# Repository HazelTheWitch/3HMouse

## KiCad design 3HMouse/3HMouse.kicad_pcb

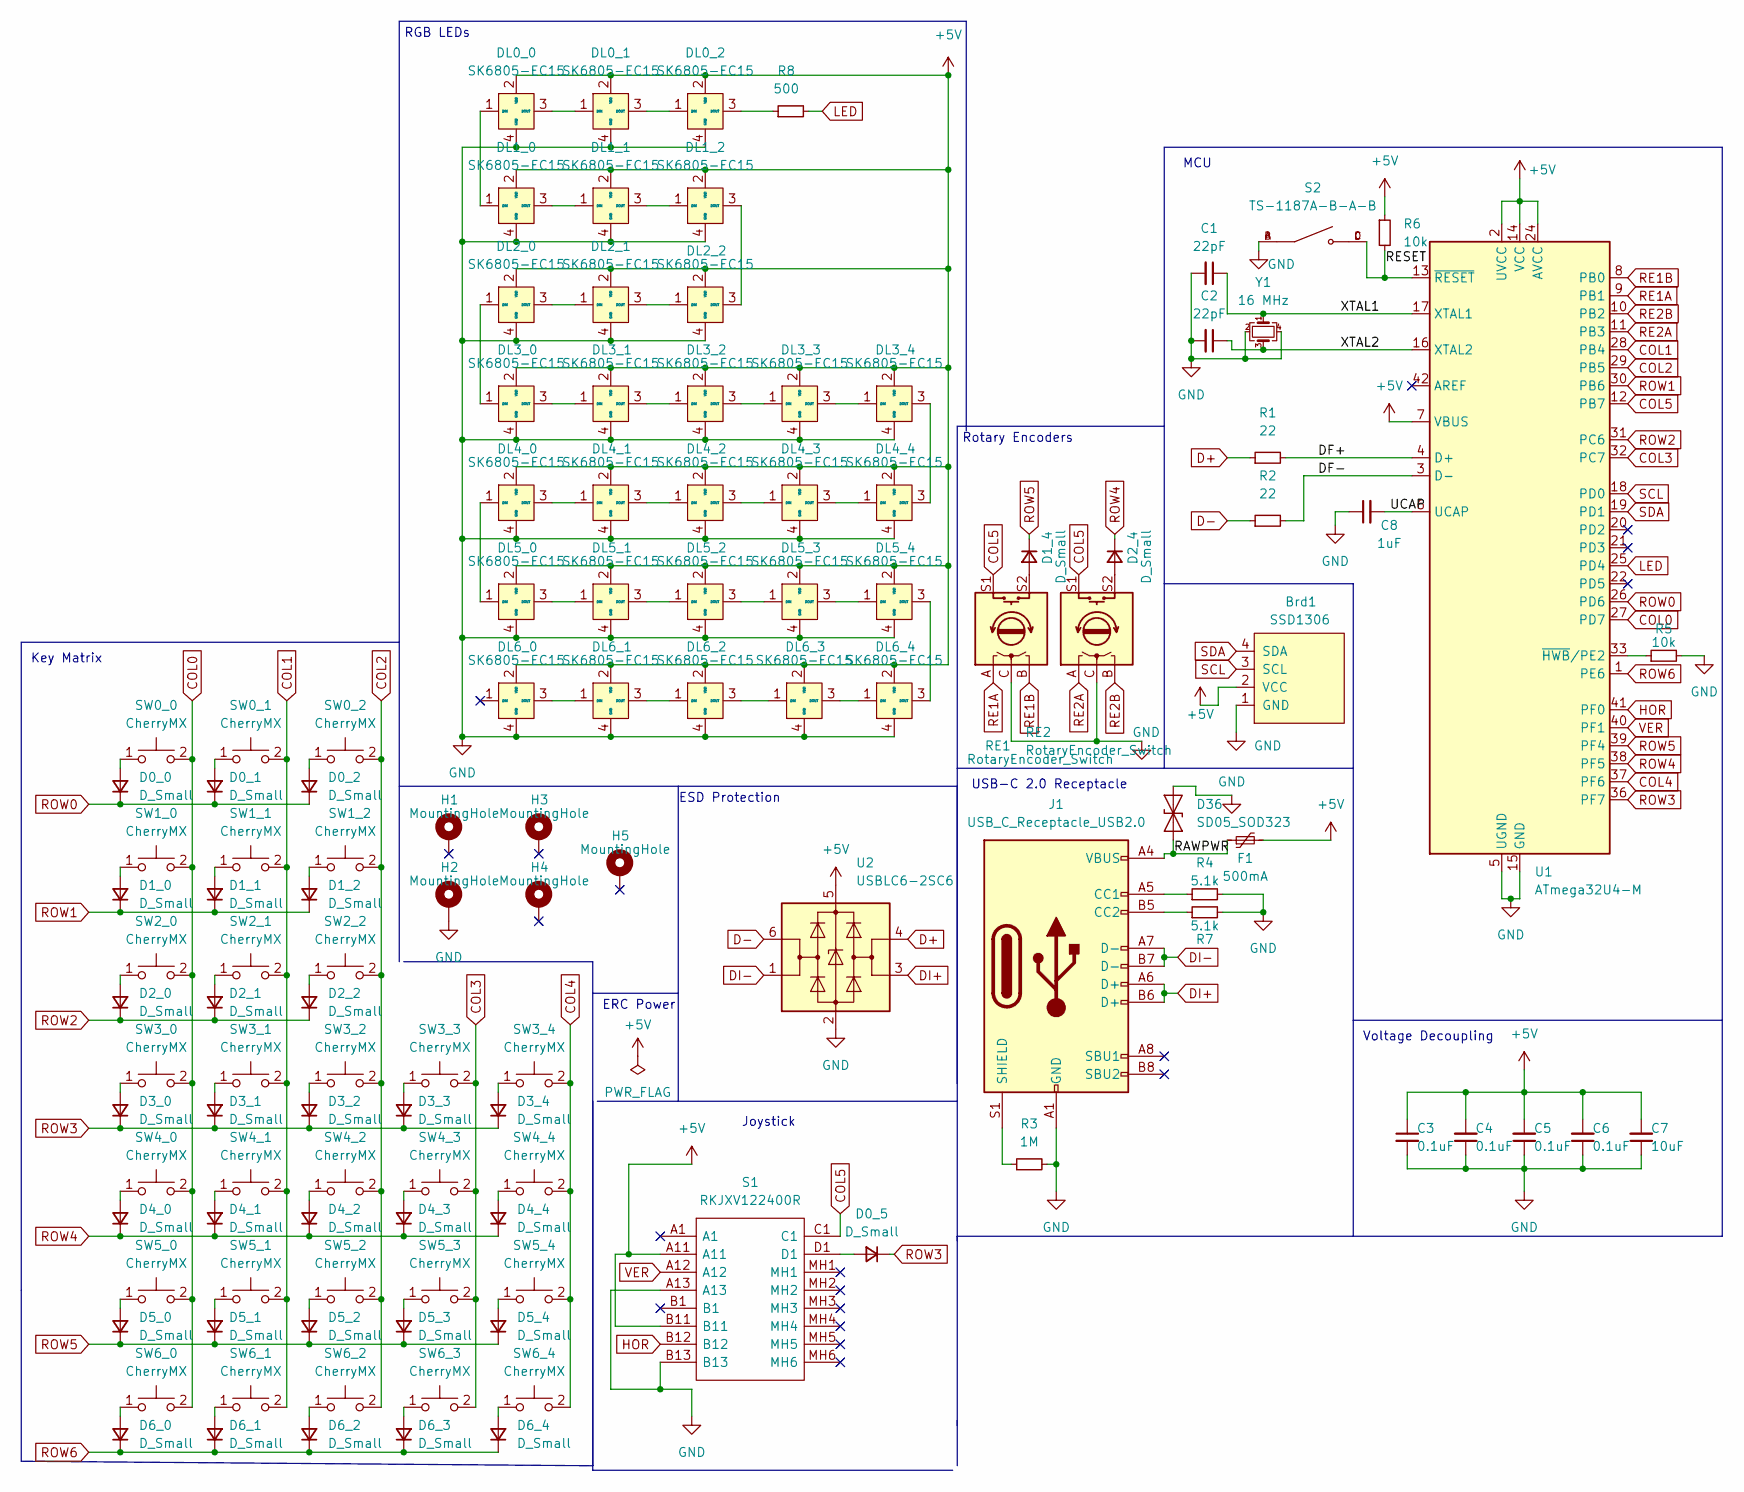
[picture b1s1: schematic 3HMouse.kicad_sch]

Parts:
Brd1: SSD1306; 128x64OLED
C1, C2: 22pF; C_0805_2012Metric
C3, C4, C5, C6: 0.1uF; C_0805_2012Metric
C7: 10uF; C_0805_2012Metric
C8: 1uF; C_0805_2012Metric
D0_0, D0_1, D0_2, D0_5, D1_0, D1_1, D1_2, D1_4, D2_0, D2_1, D2_2, D2_4, D3_0, D3_1, D3_2, D3_3, D3_4, D4_0, D4_1, D4_2, D4_3, D4_4, D5_0, D5_1, D5_2, D5_3, D5_4, D6_0, D6_1, D6_2, D6_3, D6_4: D_Small; D_SOD-123
D36: SD05_SOD323; D_SOD-323
DL0_0, DL0_1, DL0_2, DL1_0, DL1_1, DL1_2, DL2_0, DL2_1, DL2_2, DL3_0, DL3_1, DL3_2, DL3_3, DL3_4, DL4_0, DL4_1, DL4_2, DL4_3, DL4_4, DL5_0, DL5_1, DL5_2, DL5_3, DL5_4, DL6_0, DL6_1, DL6_2, DL6_3, DL6_4: SK6805-EC15
F1: 500mA; Fuse_1206_3216Metric
H1, H2, H3, H4, H5: MountingHole; MountingHole_2.2mm_M2_Pad
J1: USB_C_Receptacle_USB2.0; USB_C_Receptacle_GT-USB-7010
R1, R2: 22; R_0805_2012Metric
R3: 1M; R_0805_2012Metric
R4, R7: 5.1k; R_0805_2012Metric
R5, R6: 10k; R_0805_2012Metric
R8: 500; R_0805_2012Metric
RE1, RE2: RotaryEncoder_Switch; RotaryEncoder_Alps_EC11E-Switch_Vertical_H20mm
S1: RKJXV122400R; Mouser Part Number 688-RKJXV122400R
S2: TS-1187A-B-A-B; SW_TS-1187A-B-A-B; PARTREV A0
SW0_0, SW0_1, SW0_2, SW1_0, SW1_1, SW1_2, SW2_0, SW2_1, SW2_2, SW3_0, SW3_1, SW3_2, SW3_3, SW3_4, SW4_0, SW4_1, SW4_2, SW4_3, SW4_4, SW5_0, SW5_1, SW5_2, SW5_3, SW5_4, SW6_0, SW6_1, SW6_2, SW6_3, SW6_4: CherryMX; MXOnly-1U-Hotswap
U1: ATmega32U4-M; QFN-44-1EP_7x7mm_P0.5mm_EP5.2x5.2mm
U2: USBLC6-2SC6; SOT-23-6
Y1: 16 MHz; Crystal_SMD_3225-4Pin_3.2x2.5mm

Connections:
+5V: Brd1.2 (VCC), C3.1, C4.2, C5.2, C6.2, C7.2, DL0_0.2 (VDD), DL0_1.2 (VDD), DL0_2.2 (VDD), DL1_0.2 (VDD), DL1_1.2 (VDD), DL1_2.2 (VDD), DL2_0.2 (VDD), DL2_1.2 (VDD), DL2_2.2 (VDD), DL3_0.2 (VDD), DL3_1.2 (VDD), DL3_2.2 (VDD), DL3_3.2 (VDD), DL3_4.2 (VDD), DL4_0.2 (VDD), DL4_1.2 (VDD), DL4_2.2 (VDD), DL4_3.2 (VDD), DL4_4.2 (VDD), DL5_0.2 (VDD), DL5_1.2 (VDD), DL5_2.2 (VDD), DL5_3.2 (VDD), DL5_4.2 (VDD), DL6_0.2 (VDD), DL6_1.2 (VDD), DL6_2.2 (VDD), DL6_3.2 (VDD), DL6_4.2 (VDD), F1.2, R6.1, S1.A11, S1.B11, U1.2 (UVCC), U1.7 (VBUS), U1.14 (VCC), U1.24 (AVCC), U1.34 (VCC), U1.44 (AVCC), U2.5 (VBUS)
/DF+: R1.2, U1.4 (D+)
/DF-: R2.2, U1.3 (D-)
/RAWPWR: D36.1 (A1), F1.1, J1.A4 (VBUS), J1.A9 (VBUS), J1.B4 (VBUS), J1.B9 (VBUS)
/RESET: R6.2, S2.C, S2.D, U1.13 (~RESET)
/UCAP: C8.2, U1.6 (UCAP)
/XTAL1: C1.1, U1.17 (XTAL1), Y1.1
/XTAL2: C2.1, U1.16 (XTAL2), Y1.3
COL0: SW0_0.2, SW1_0.2, SW2_0.2, SW3_0.2, SW4_0.2, SW5_0.2, SW6_0.2, U1.27 (PD7)
COL1: SW0_1.2, SW1_1.2, SW2_1.2, SW3_1.2, SW4_1.2, SW5_1.2, SW6_1.2, U1.28 (PB4)
COL2: SW0_2.2, SW1_2.2, SW2_2.2, SW3_2.2, SW4_2.2, SW5_2.2, SW6_2.2, U1.29 (PB5)
COL3: SW3_3.2, SW4_3.2, SW5_3.2, SW6_3.2, U1.32 (PC7)
COL4: SW3_4.2, SW4_4.2, SW5_4.2, SW6_4.2, U1.37 (PF6)
COL5: RE1.S1, RE2.S1, S1.C1, U1.12 (PB7)
D+: R1.1, U2.4 (I/O2)
D-: R2.1, U2.6 (I/O1)
DI+: J1.A6 (D+), J1.B6 (D+), U2.3 (I/O2)
DI-: J1.A7 (D-), J1.B7 (D-), U2.1 (I/O1)
GND: Brd1.1 (GND), C1.2, C2.2, C3.2, C4.1, C5.1, C6.1, C7.1, C8.1, D36.2 (A2), DL0_0.4 (GND), DL0_1.4 (GND), DL0_2.4 (GND), DL1_0.4 (GND), DL1_1.4 (GND), DL1_2.4 (GND), DL2_0.4 (GND), DL2_1.4 (GND), DL2_2.4 (GND), DL3_0.4 (GND), DL3_1.4 (GND), DL3_2.4 (GND), DL3_3.4 (GND), DL3_4.4 (GND), DL4_0.4 (GND), DL4_1.4 (GND), DL4_2.4 (GND), DL4_3.4 (GND), DL4_4.4 (GND), DL5_0.4 (GND), DL5_1.4 (GND), DL5_2.4 (GND), DL5_3.4 (GND), DL5_4.4 (GND), DL6_0.4 (GND), DL6_1.4 (GND), DL6_2.4 (GND), DL6_3.4 (GND), DL6_4.4 (GND), H2.1, J1.A1 (GND), J1.A12 (GND), J1.B1 (GND), J1.B12 (GND), R3.2, R4.2, R5.2, R7.2, RE1.C, RE2.C, S1.A13, S1.B13, S2.A, S2.B, U1.5 (UGND), U1.15 (GND), U1.23 (GND), U1.35 (GND), U1.43 (GND), U1.45 (GND), U2.2 (GND), Y1.2, Y1.4
HOR: S1.B12, U1.41 (PF0)
LED: R8.2, U1.25 (PD4)
unnamed: D0_0.2 (A), SW0_0.1
unnamed: D0_1.2 (A), SW0_1.1
unnamed: D0_2.2 (A), SW0_2.1
unnamed: D0_5.2 (A), S1.D1
unnamed: D1_0.2 (A), SW1_0.1
unnamed: D1_1.2 (A), SW1_1.1
unnamed: D1_2.2 (A), SW1_2.1
unnamed: D1_4.2 (A), RE1.S2
unnamed: D2_0.2 (A), SW2_0.1
unnamed: D2_1.2 (A), SW2_1.1
unnamed: D2_2.2 (A), SW2_2.1
unnamed: D2_4.2 (A), RE2.S2
unnamed: D3_0.2 (A), SW3_0.1
unnamed: D3_1.2 (A), SW3_1.1
unnamed: D3_2.2 (A), SW3_2.1
unnamed: D3_3.2 (A), SW3_3.1
unnamed: D3_4.2 (A), SW3_4.1
unnamed: D4_0.2 (A), SW4_0.1
unnamed: D4_1.2 (A), SW4_1.1
unnamed: D4_2.2 (A), SW4_2.1
unnamed: D4_3.2 (A), SW4_3.1
unnamed: D4_4.2 (A), SW4_4.1
unnamed: D5_0.2 (A), SW5_0.1
unnamed: D5_1.2 (A), SW5_1.1
unnamed: D5_2.2 (A), SW5_2.1
unnamed: D5_3.2 (A), SW5_3.1
unnamed: D5_4.2 (A), SW5_4.1
unnamed: D6_0.2 (A), SW6_0.1
unnamed: D6_1.2 (A), SW6_1.1
unnamed: D6_2.2 (A), SW6_2.1
unnamed: D6_3.2 (A), SW6_3.1
unnamed: D6_4.2 (A), SW6_4.1
unnamed: DL0_0.1 (DIN), DL1_0.1 (DIN)
unnamed: DL0_0.3 (DOUT), DL0_1.1 (DIN)
unnamed: DL0_1.3 (DOUT), DL0_2.1 (DIN)
unnamed: DL0_2.3 (DOUT), R8.1
unnamed: DL1_0.3 (DOUT), DL1_1.1 (DIN)
unnamed: DL1_1.3 (DOUT), DL1_2.1 (DIN)
unnamed: DL1_2.3 (DOUT), DL2_2.3 (DOUT)
unnamed: DL2_0.1 (DIN), DL3_0.1 (DIN)
unnamed: DL2_0.3 (DOUT), DL2_1.1 (DIN)
unnamed: DL2_1.3 (DOUT), DL2_2.1 (DIN)
unnamed: DL3_0.3 (DOUT), DL3_1.1 (DIN)
unnamed: DL3_1.3 (DOUT), DL3_2.1 (DIN)
unnamed: DL3_2.3 (DOUT), DL3_3.1 (DIN)
unnamed: DL3_3.3 (DOUT), DL3_4.1 (DIN)
unnamed: DL3_4.3 (DOUT), DL4_4.3 (DOUT)
unnamed: DL4_0.1 (DIN), DL5_0.1 (DIN)
unnamed: DL4_0.3 (DOUT), DL4_1.1 (DIN)
unnamed: DL4_1.3 (DOUT), DL4_2.1 (DIN)
unnamed: DL4_2.3 (DOUT), DL4_3.1 (DIN)
unnamed: DL4_3.3 (DOUT), DL4_4.1 (DIN)
unnamed: DL5_0.3 (DOUT), DL5_1.1 (DIN)
unnamed: DL5_1.3 (DOUT), DL5_2.1 (DIN)
unnamed: DL5_2.3 (DOUT), DL5_3.1 (DIN)
unnamed: DL5_3.3 (DOUT), DL5_4.1 (DIN)
unnamed: DL5_4.3 (DOUT), DL6_4.3 (DOUT)
unnamed: DL6_0.3 (DOUT), DL6_1.1 (DIN)
unnamed: DL6_1.3 (DOUT), DL6_2.1 (DIN)
unnamed: DL6_2.3 (DOUT), DL6_3.1 (DIN)
unnamed: DL6_3.3 (DOUT), DL6_4.1 (DIN)
unnamed: J1.A5 (CC1), R4.1
unnamed: J1.B5 (CC2), R7.1
unnamed: J1.S1 (SHIELD), R3.1
unnamed: R5.1, U1.33 (~HWB/PE2)
RE1A: RE1.A, U1.9 (PB1)
RE1B: RE1.B, U1.8 (PB0)
RE2A: RE2.A, U1.11 (PB3)
RE2B: RE2.B, U1.10 (PB2)
ROW0: D0_0.1 (K), D0_1.1 (K), D0_2.1 (K), U1.26 (PD6)
ROW1: D1_0.1 (K), D1_1.1 (K), D1_2.1 (K), U1.30 (PB6)
ROW2: D2_0.1 (K), D2_1.1 (K), D2_2.1 (K), U1.31 (PC6)
ROW3: D0_5.1 (K), D3_0.1 (K), D3_1.1 (K), D3_2.1 (K), D3_3.1 (K), D3_4.1 (K), U1.36 (PF7)
ROW4: D2_4.1 (K), D4_0.1 (K), D4_1.1 (K), D4_2.1 (K), D4_3.1 (K), D4_4.1 (K), U1.38 (PF5)
ROW5: D1_4.1 (K), D5_0.1 (K), D5_1.1 (K), D5_2.1 (K), D5_3.1 (K), D5_4.1 (K), U1.39 (PF4)
ROW6: D6_0.1 (K), D6_1.1 (K), D6_2.1 (K), D6_3.1 (K), D6_4.1 (K), U1.1 (PE6)
SCL: Brd1.3 (SCL), U1.18 (PD0)
SDA: Brd1.4 (SDA), U1.19 (PD1)
VER: S1.A12, U1.40 (PF1)

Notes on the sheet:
RGB LEDs
Joystick
ESD Protection
Rotary Encoders
Voltage Decoupling
MCU
Key Matrix
USB-C 2.0 Receptacle
ERC Power

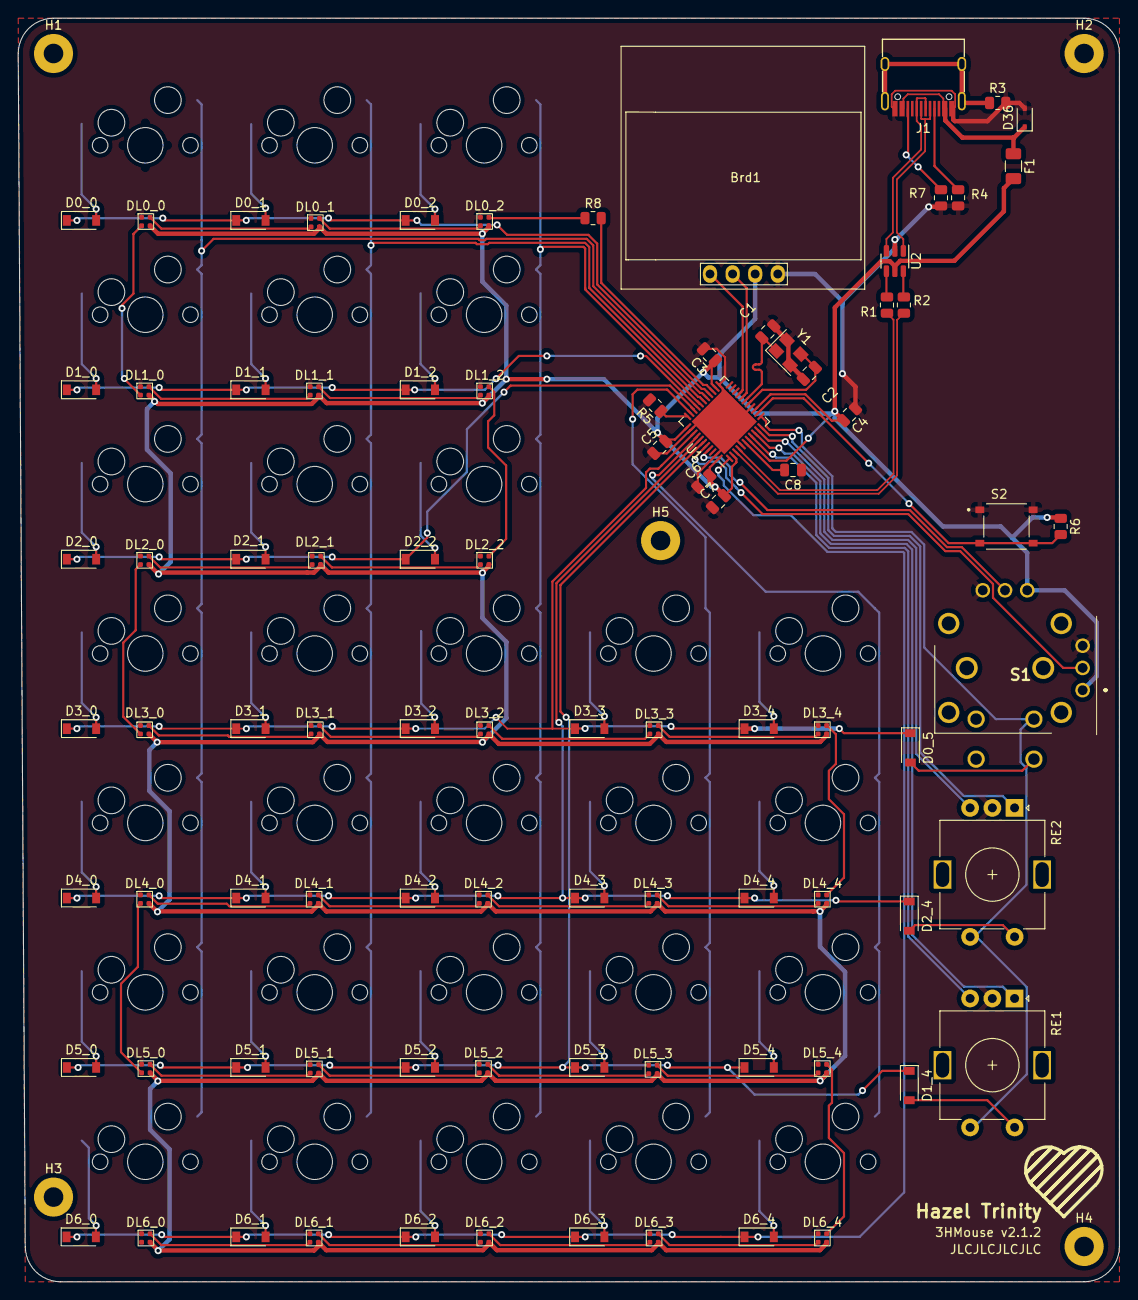
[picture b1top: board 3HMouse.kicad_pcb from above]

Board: 2 copper layers, 123.8 x 142.1 mm, 122 parts (0 on the bottom side), 100 nets.

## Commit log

2022-05-15 Initial Project Setup
2022-05-15 Added Firmware Submodule
2022-05-15 Initial Schematic Setup
2022-05-15 Updated Numbering for switches
2022-05-15 v0.1.0
2022-05-17 Added ESD Protection and wired Joystick and Encoders
2022-05-17 Added NC to Schematic
2022-05-17 Finished Initial Routing
2022-05-17 v0.2.0
2022-05-17 v0.2.1
2022-05-17 v0.2.1 update
2022-05-17 v0.4.0
2022-05-17 v0.4.0 final
2022-05-18 Placements done for v2
2022-05-18 LED and switch routing
2022-05-18 v2 Done
2022-05-18 v2.1.0
2022-05-19 v2.1.1
